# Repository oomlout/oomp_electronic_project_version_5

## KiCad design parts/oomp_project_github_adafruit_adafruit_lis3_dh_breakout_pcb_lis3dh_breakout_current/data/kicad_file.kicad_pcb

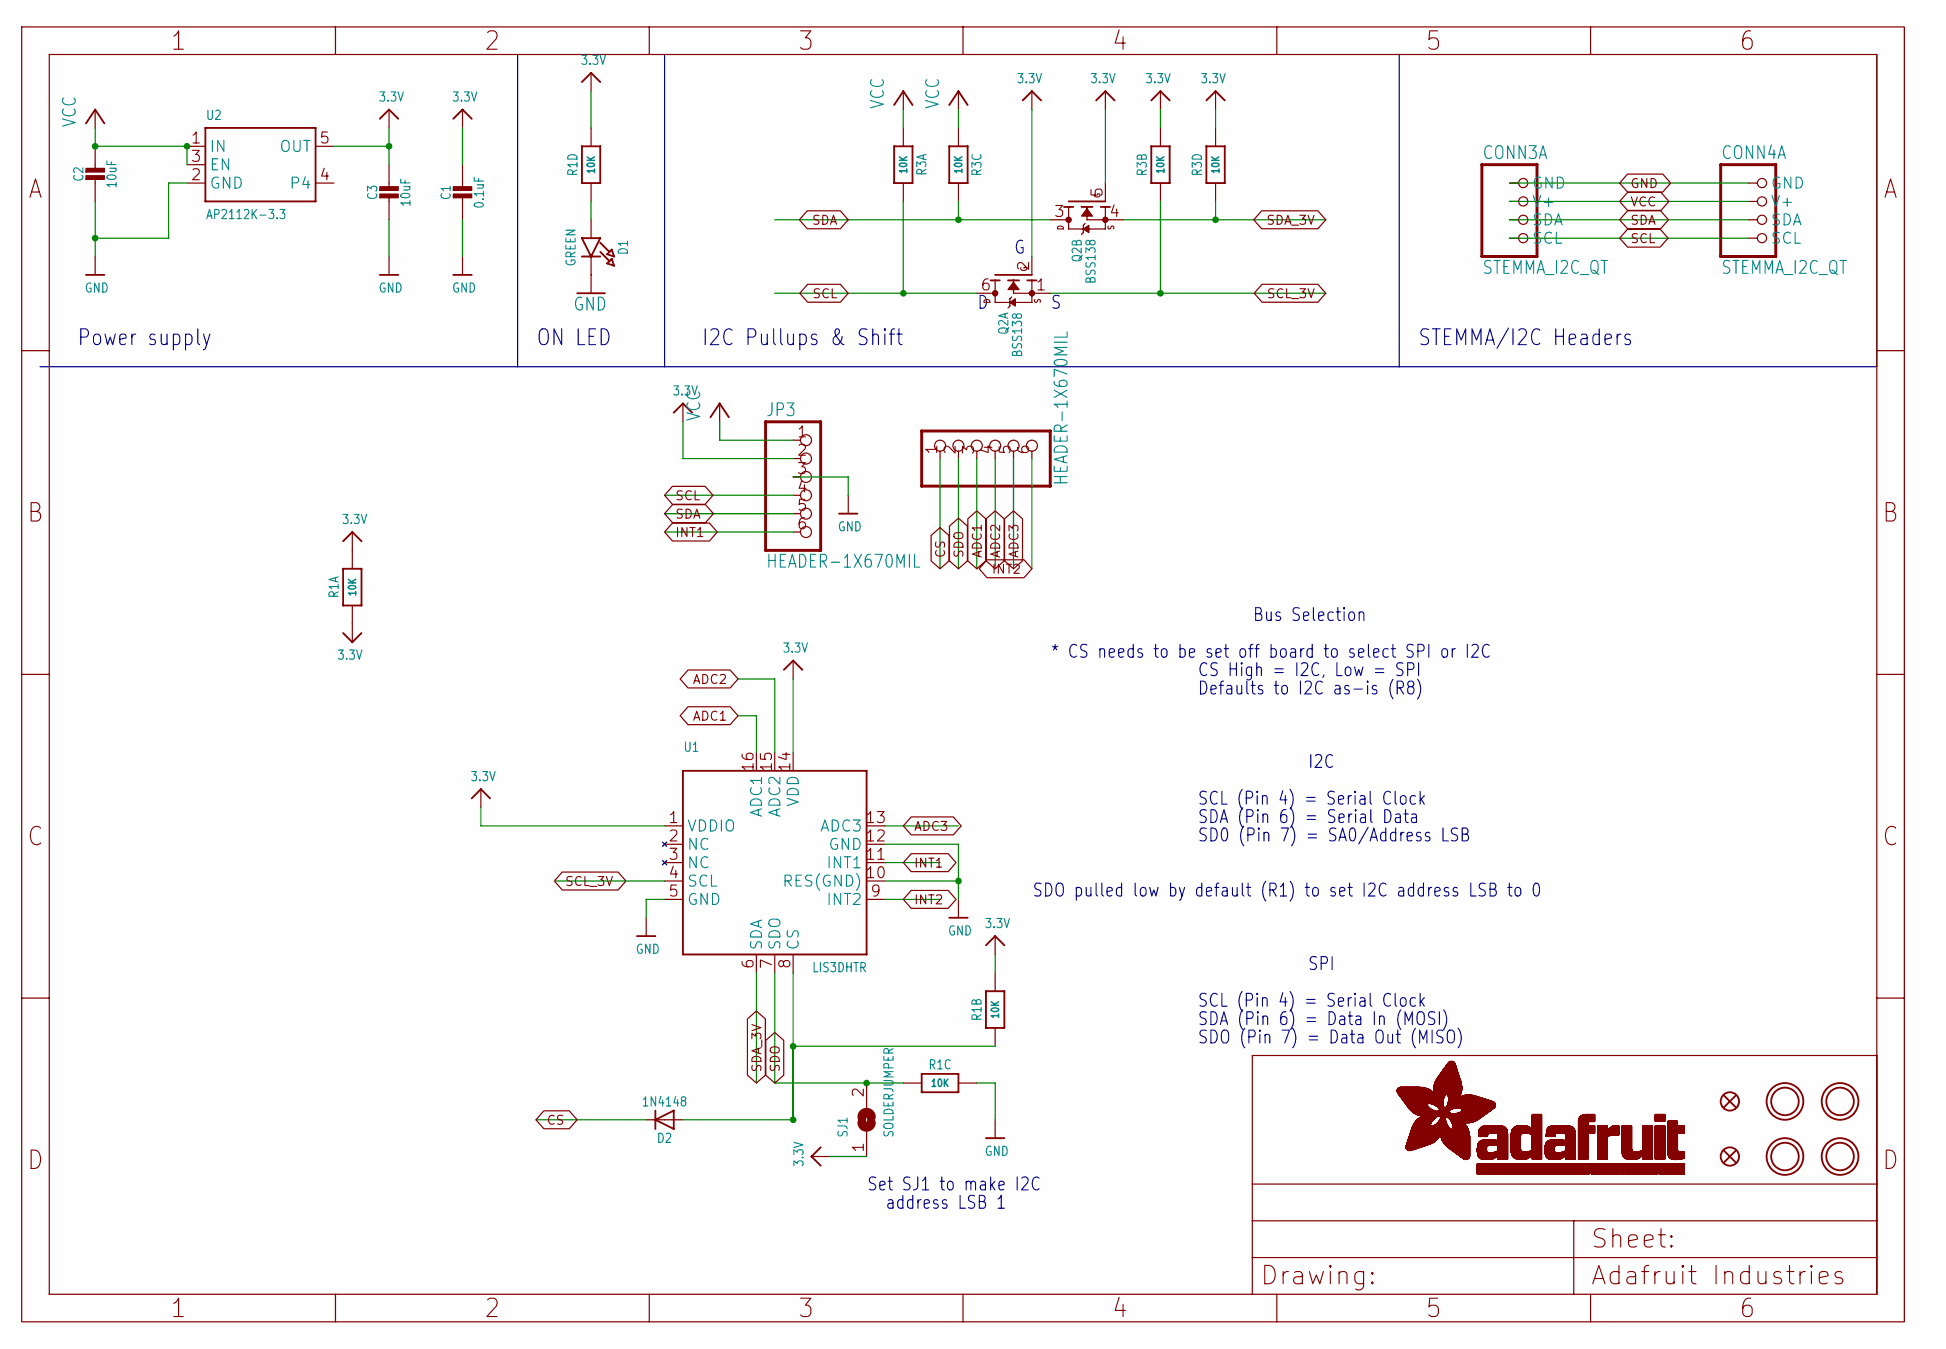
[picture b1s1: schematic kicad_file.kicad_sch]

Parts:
C1: 0.1uF; 0603-NO
C2, C3: 10uF; 0805-NO
CONN3, CONN4: STEMMA_I2C_QT; JST_SH4
D1: GREEN; CHIPLED_0603_NOOUTLINE
D2: 1N4148; SOD-323
FID3, FID4: FIDUCIAL_1MM
JP2, JP3: HEADER-1X670MIL; 1X06_ROUND_70
Q2: BSS138; SOT363
R1, R3: 10K; RESPACK_4X0603
SJ1: SOLDERJUMPER; SOLDERJUMPER_ARROW_NOPASTE
U1: LIS3DHTR; LGA16_3X3MM
U2: AP2112K-3.3; SOT23-5
U$1, U$17, U$19, U$21: MOUNTINGHOLE2.5; MOUNTINGHOLE_2.5_PLATED

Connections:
3.3V: C1.1, C3.1, JP3.2, Q2.2 (G), Q2.5 (G), R1.1, R1.5 (2), R1.7 (2), R1.8 (2), R3.2 (1), R3.4 (1), SJ1.1, U1.1 (VDDIO), U1.14 (VDD), U2.5 (OUT)
ADC1: JP2.3, U1.16 (ADC1)
ADC2: JP2.4, U1.15 (ADC2)
ADC3: JP2.5, U1.13 (ADC3)
CS: D2.C, JP2.1
GND: C1.2, C2.2, C3.2, CONN3.1 (GND), CONN4.1 (GND), D1.C, JP3.3, R1.6 (2), U1.5 (GND), U1.10 (RES(GND)), U1.12 (GND), U2.2 (GND)
INT1: JP3.6, U1.11 (INT1)
INT2: JP2.6, U1.9 (INT2)
unnamed: D1.A, R1.4 (1)
unnamed: D2.A, R1.2 (1), U1.8 (CS)
SCL: CONN3.4 (SCL), CONN4.4 (SCL), JP3.4, Q2.6 (D), R3.8 (2)
SCL_3V: Q2.1 (S), R3.7 (2), U1.4 (SCL)
SDA: CONN3.3 (SDA), CONN4.3 (SDA), JP3.5, Q2.3 (D), R3.6 (2)
SDA_3V: Q2.4 (S), R3.5 (2), U1.6 (SDA)
SDO: JP2.2, R1.3 (1), SJ1.2, U1.7 (SDO)
VCC: C2.1, CONN3.2 (V+), CONN4.2 (V+), JP3.1, R3.1, R3.3 (1), U2.1 (IN), U2.3 (EN)

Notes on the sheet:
SD0 (Pin 7) = SA0/Address LSB
SDO pulled low by default (R1) to set I2C address LSB to 0
STEMMA/I2C Headers
Bus Selection
SPI
I2C Pullups & Shift
SDA (Pin 6) = Serial Data
SDA (Pin 6) = Data In (MOSI)
Defaults to I2C as-is (R8)
I2C
Set SJ1 to make I2C
address LSB 1
CS High = I2C, Low = SPI
SDO (Pin 7) = Data Out (MISO)
* CS needs to be set off board to select SPI or I2C
Power supply
SCL (Pin 4) = Serial Clock
ON LED

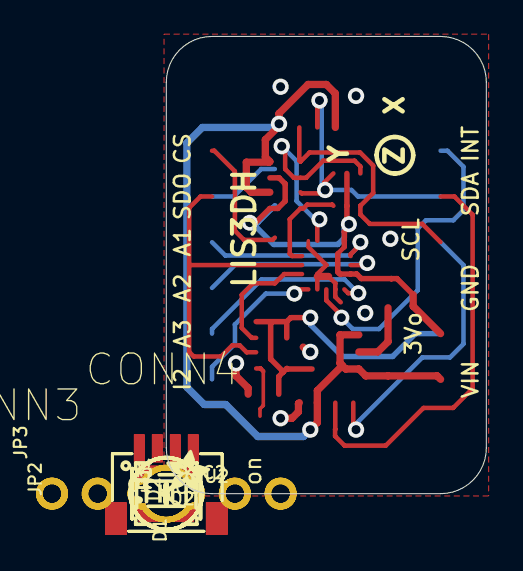
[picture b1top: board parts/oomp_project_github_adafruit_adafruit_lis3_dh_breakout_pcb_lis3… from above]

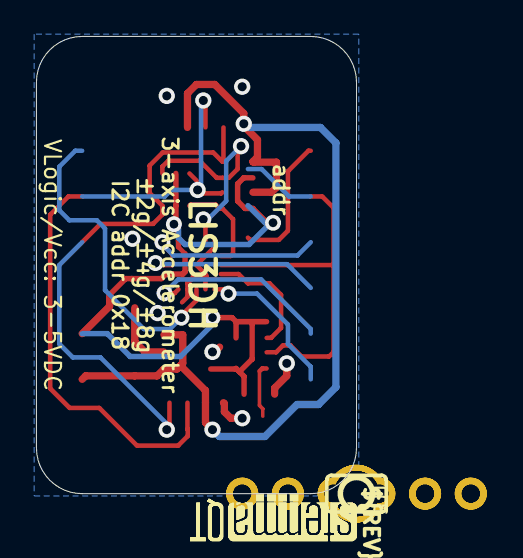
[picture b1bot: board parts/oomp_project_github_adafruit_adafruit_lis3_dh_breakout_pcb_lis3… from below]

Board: 2 copper layers, 17.8 x 25.4 mm, 25 parts (4 on the bottom side), 16 nets.

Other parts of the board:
U$12: ADAFRUIT_2.5MM
U$25: PCBFEAT-REV-040
U$30, U$31: STEMMAQT

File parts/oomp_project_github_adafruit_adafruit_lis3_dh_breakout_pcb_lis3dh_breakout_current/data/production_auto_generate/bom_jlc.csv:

Comment,Designator,Footprint,LCSC Part #
,"JP2,JP3",Adafruit LIS3DH-import-fps:1X06_ROUND_70,C37208
,U$12,Adafruit LIS3DH-import-fps:ADAFRUIT_2.5MM,
,U$25,Adafruit LIS3DH-import-fps:PCBFEAT-REV-040,
,"U$30,U$31",Adafruit LIS3DH-import-fps:STEMMAQT,
0.1uF,C1,Adafruit LIS3DH-import-fps:0603-NO,C14663
10K,"R1,R3",Adafruit LIS3DH-import-fps:RESPACK_4X0603,C98220
10uF,"C2,C3",Adafruit LIS3DH-import-fps:0805-NO,
1N4148,D2,Adafruit LIS3DH-import-fps:SOD-323,
AP2112K-3.3,U2,Adafruit LIS3DH-import-fps:SOT23-5,
BSS138,Q2,Adafruit LIS3DH-import-fps:SOT363,
GREEN,D1,Adafruit LIS3DH-import-fps:CHIPLED_0603_NOOUTLINE,
LIS3DHTR,U1,Adafruit LIS3DH-import-fps:LGA16_3X3MM,
STEMMA_I2C_QT,"CONN3,CONN4",Adafruit LIS3DH-import-fps:JST_SH4,C160404

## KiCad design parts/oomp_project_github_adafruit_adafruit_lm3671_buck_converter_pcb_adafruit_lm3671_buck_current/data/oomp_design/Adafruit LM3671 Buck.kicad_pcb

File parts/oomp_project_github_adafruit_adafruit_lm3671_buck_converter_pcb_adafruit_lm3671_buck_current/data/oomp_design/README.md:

# OOMP KiCad design copy

Open `Adafruit LM3671 Buck.kicad_pro` (or the `.kicad_pcb` / `.kicad_sch`) in KiCad. Local OOMP libraries are under `libraries/`. Original inputs are preserved in [../original/](../original/).

Only verified unchanged installed KiCad defaults were renamed. Modified, custom, unmatched and unavailable items remain unchanged. Soldering variants are never swapped during conversion. Existing pad coordinates, nets and UUIDs are preserved.

See [conversion_report.yaml](conversion_report.yaml) for every conversion and skip. Copy this directory before editing; regeneration refuses to overwrite edited design files.

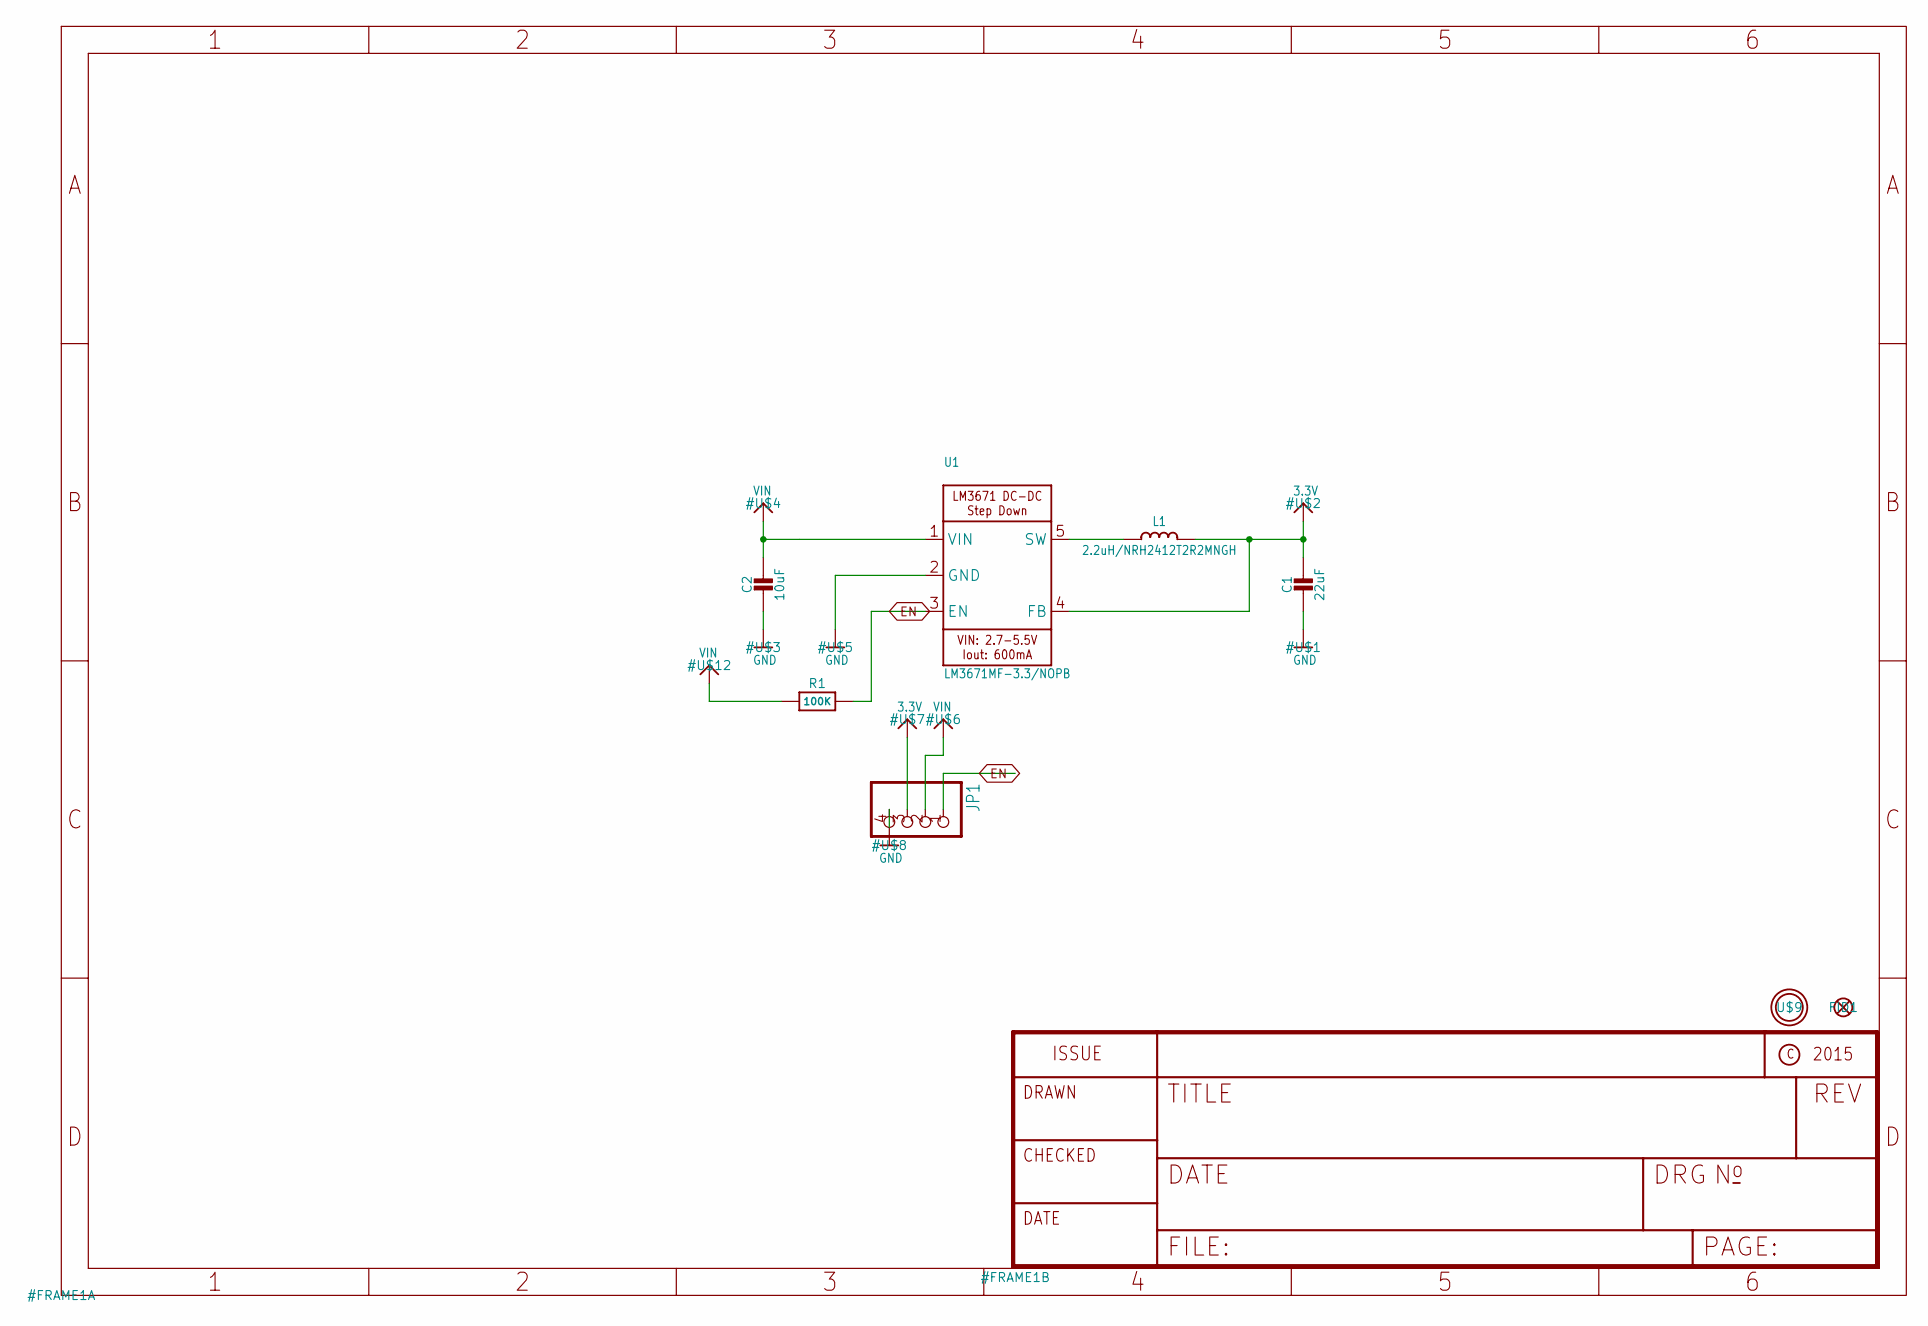
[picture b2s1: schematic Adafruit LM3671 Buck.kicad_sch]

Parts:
C1: 22uF; 0805-NO
C2: 10uF; 0805-NO
FID1: FIDUCIAL""; FIDUCIAL_1MM
JP1: HEADER-1X4ROUND; 1X04_ROUND
L1: 2.2uH/NRH2412T2R2MNGH; INDUCTOR_TAIYOYUDEN_NRH2412T
R1: 100K; 0805-NO
U1: LM3671MF-3.3/NOPB; SOT23-5
U$9: MOUNTINGHOLE2.5; MOUNTINGHOLE_2.5_PLATED

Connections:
3.3V: C1.1, JP1.3, L1.2, U1.4 (FB)
EN: JP1.1, R1.2, U1.3 (EN)
GND: C1.2, C2.2, JP1.4, U1.2 (GND)
unnamed: L1.1, U1.5 (SW)
VIN: C2.1, JP1.2, R1.1, U1.1 (VIN)

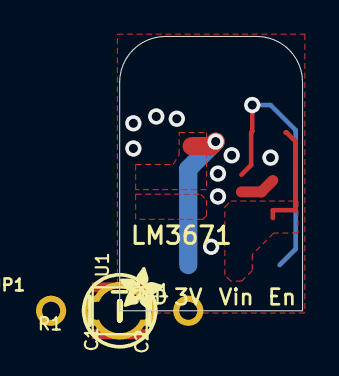
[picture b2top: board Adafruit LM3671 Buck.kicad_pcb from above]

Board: 2 copper layers, 10.2 x 15.2 mm, 10 parts (1 on the bottom side), 5 nets.

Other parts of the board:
U$10: PCBFEAT-REV-040
U$11: ADAFRUIT_2.5MM

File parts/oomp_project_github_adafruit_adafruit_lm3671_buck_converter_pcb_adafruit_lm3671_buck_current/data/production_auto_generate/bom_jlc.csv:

Comment,Designator,Footprint,LCSC Part #
,JP1,Adafruit LM3671 Buck-import-fps:1X04_ROUND,C42431795
,U$11,Adafruit LM3671 Buck-import-fps:ADAFRUIT_2.5MM,
,U$10,Adafruit LM3671 Buck-import-fps:PCBFEAT-REV-040,
100K,R1,Adafruit LM3671 Buck-import-fps:0805-NO,C149504
10uF,C2,Adafruit LM3671 Buck-import-fps:0805-NO,
2.2uH/NRH2412T2R2MNGH,L1,Adafruit LM3671 Buck-import-fps:INDUCTOR_TAIYOYUDEN_NRH2412T,
22uF,C1,Adafruit LM3671 Buck-import-fps:0805-NO,
LM3671MF-3.3/NOPB,U1,Adafruit LM3671 Buck-import-fps:SOT23-5,

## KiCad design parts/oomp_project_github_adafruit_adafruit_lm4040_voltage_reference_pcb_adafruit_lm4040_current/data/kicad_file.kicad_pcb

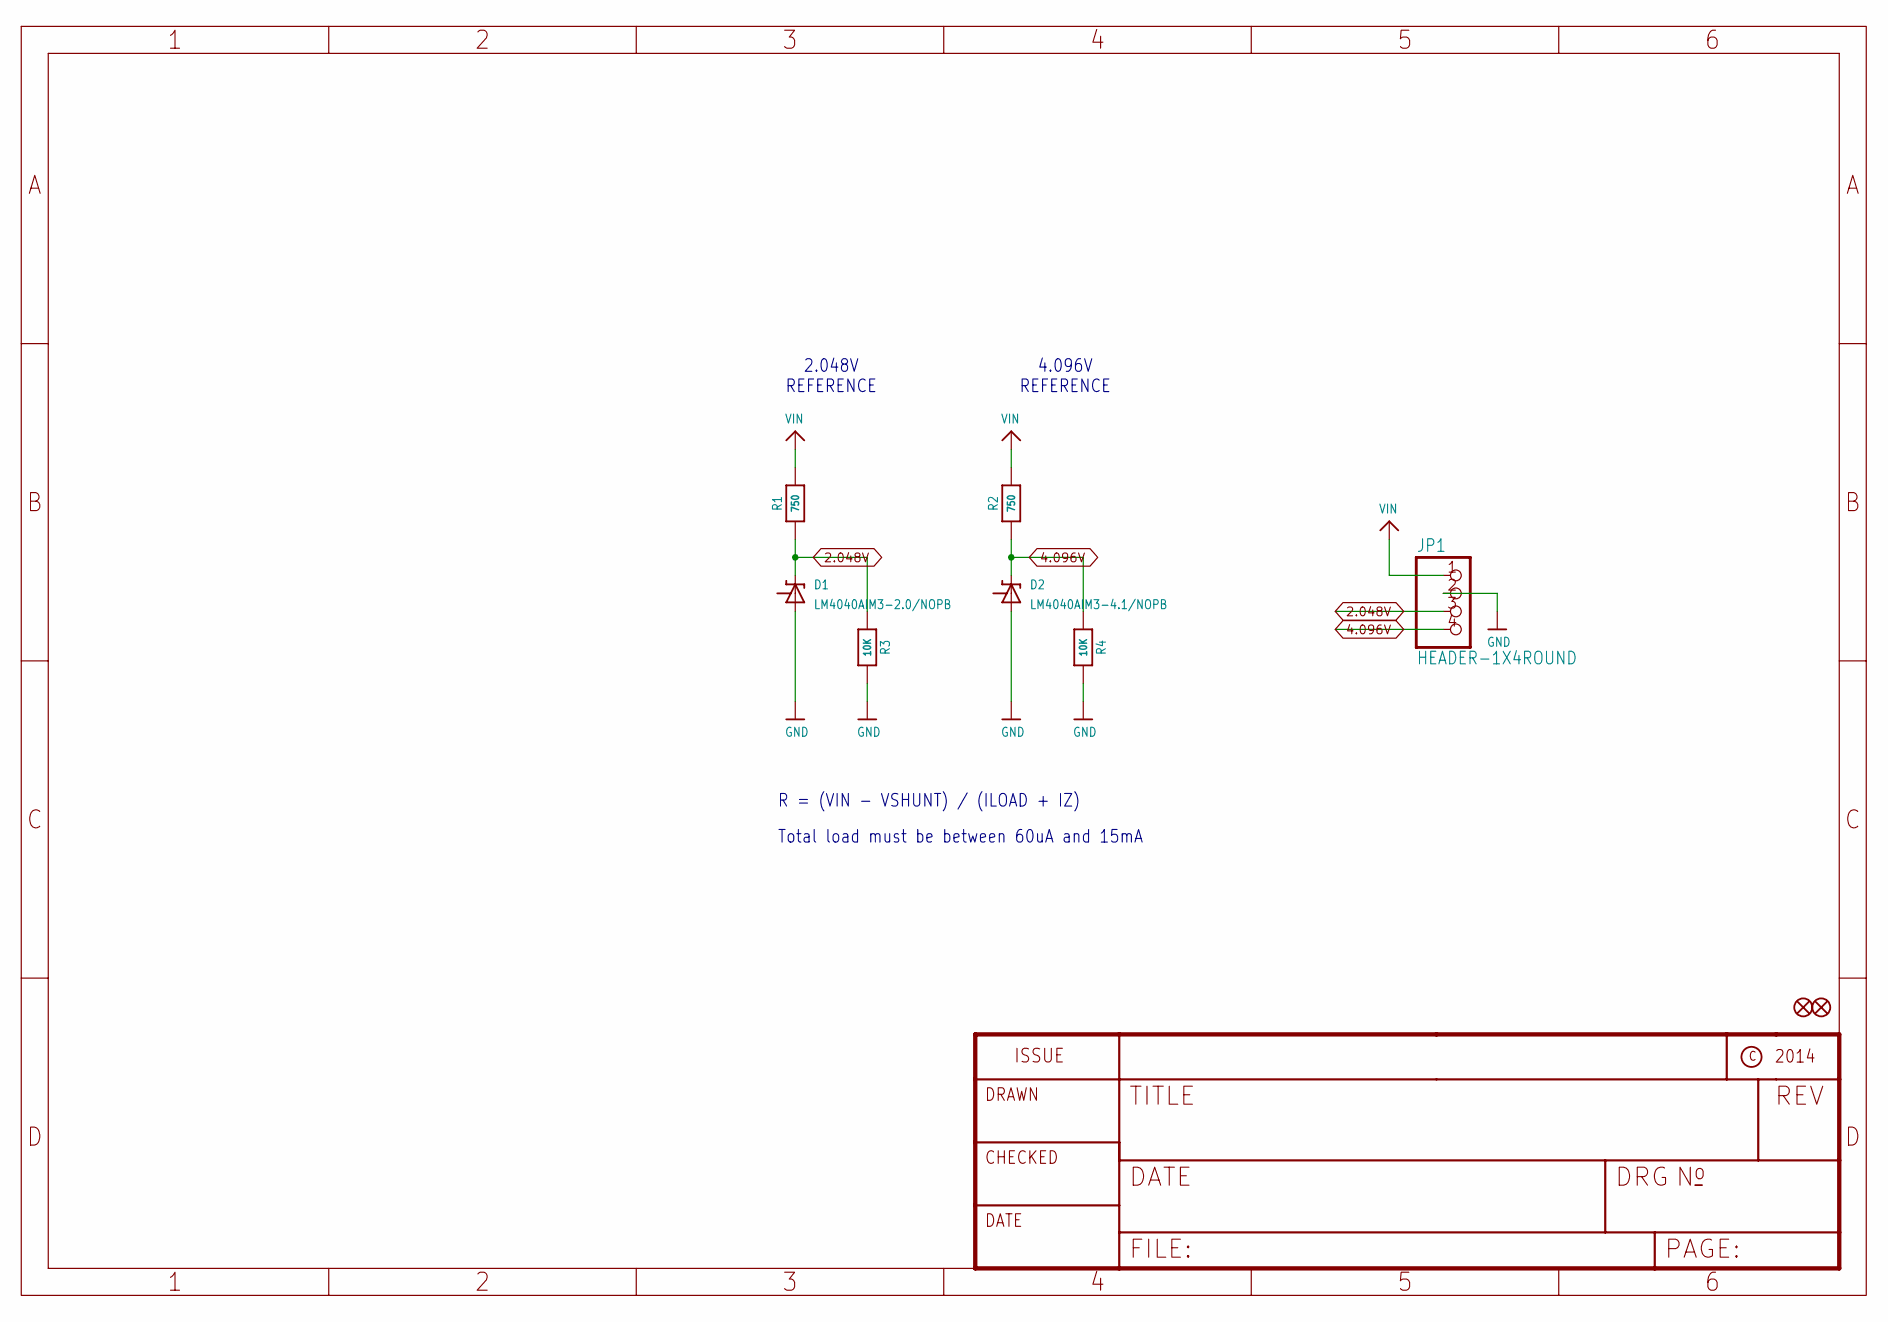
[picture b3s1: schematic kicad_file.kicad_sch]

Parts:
D1: LM4040AIM3-2.0/NOPB; SOT23-R
D2: LM4040AIM3-4.1/NOPB; SOT23-R
FID1, FID2: FIDUCIAL""; FIDUCIAL_1MM
JP1: HEADER-1X4ROUND; 1X04_ROUND
R1, R2: 750; 0805-NO
R3, R4: 10K; 0805-NO

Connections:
2.048V: D1.1 (+), JP1.3, R1.1, R3.1
4.096V: D2.1 (+), JP1.4, R2.1, R4.1
GND: D1.2 (-), D2.2 (-), JP1.2, R3.2, R4.2
VIN: JP1.1, R1.2, R2.2

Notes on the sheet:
2.048V REFERENCE
Total load must be between 60uA and 15mA
R = (VIN - VSHUNT) / (ILOAD + IZ)
4.096V REFERENCE

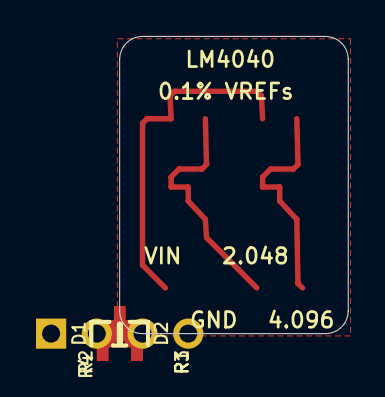
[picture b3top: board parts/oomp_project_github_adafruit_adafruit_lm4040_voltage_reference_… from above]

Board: 2 copper layers, 12.7 x 16.5 mm, 10 parts (1 on the bottom side), 4 nets.

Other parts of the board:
U$5: ADAFRUIT_5MM

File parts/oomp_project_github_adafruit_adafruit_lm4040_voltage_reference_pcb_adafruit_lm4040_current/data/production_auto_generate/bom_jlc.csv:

Comment,Designator,Footprint,LCSC Part #
,JP1,Adafruit LM4040-import-fps:1X04_ROUND,C42431795
,U$5,Adafruit LM4040-import-fps:ADAFRUIT_5MM,
10K,"R3,R4",Adafruit LM4040-import-fps:0805-NO,C17414
750,"R1,R2",Adafruit LM4040-import-fps:0805-NO,C2907285
LM4040AIM3-2.0/NOPB,D1,Adafruit LM4040-import-fps:SOT23-R,
LM4040AIM3-4.1/NOPB,D2,Adafruit LM4040-import-fps:SOT23-R,
